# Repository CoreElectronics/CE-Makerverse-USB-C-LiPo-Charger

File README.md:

# Makerverse™ USB-C LiPo Charger

This is the repo for the Core Electronics [USB-C LiPo Charger](https://core-electronics.com.au/catalog/product/view/sku/ce08374).

The PCB layout project requires KiCAD 6.0 or newer to view. The schematic is provided in PDF format in the Documents folder.

## License
This project is open source - please review the LICENSE.md file for further licensing information.

If you have any technical questions, or concerns about licensing, please contact technical support on the [Core Electronics forums](https://forum.core-electronics.com.au/).

*\"PiicoDev\" and the PiicoDev logo are trademarks of Core Electronics Pty Ltd.*

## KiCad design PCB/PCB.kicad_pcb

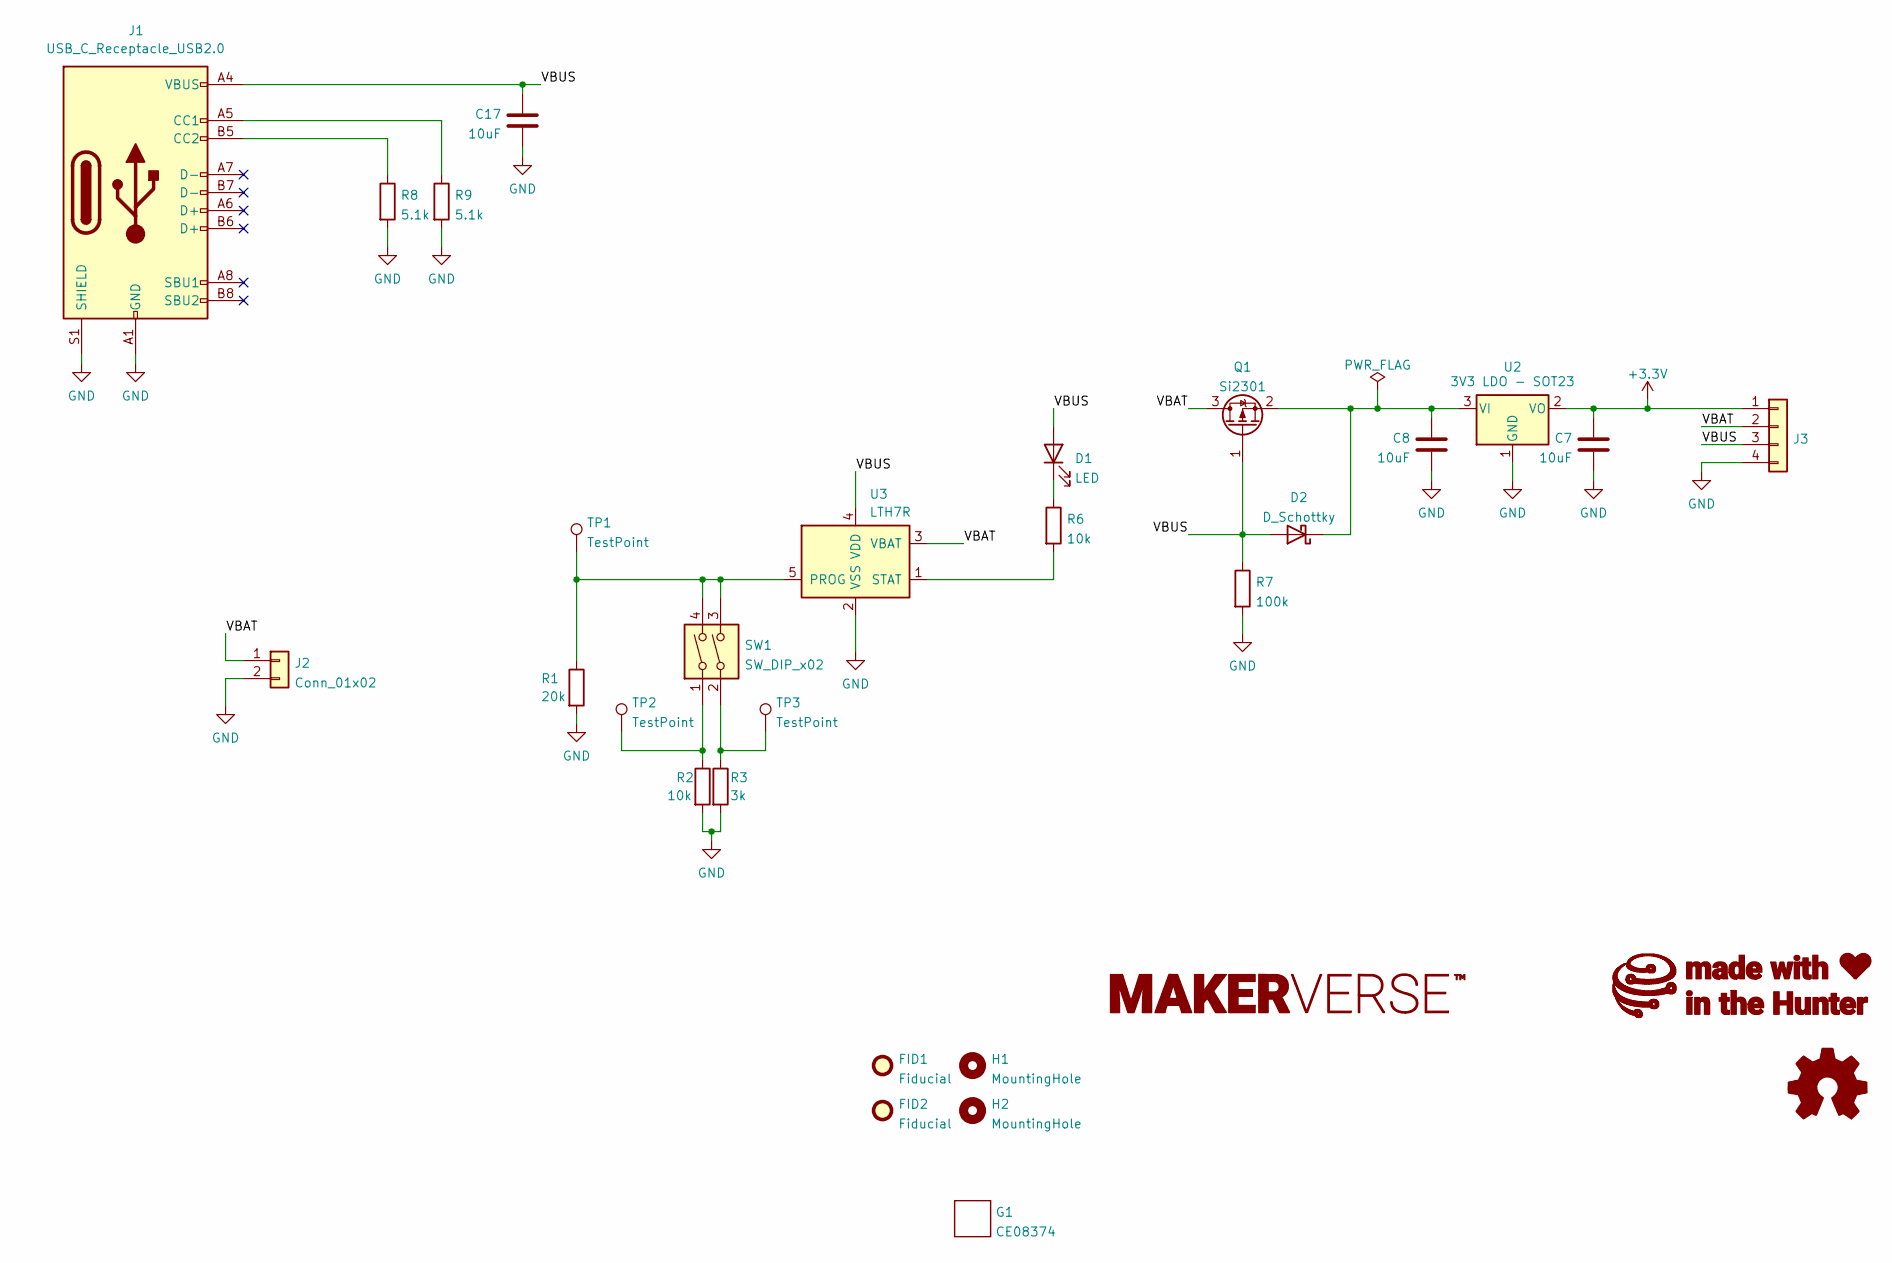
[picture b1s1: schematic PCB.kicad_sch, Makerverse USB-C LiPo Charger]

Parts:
C7, C8, C17: 10uF; C_0603_1608Metric
D1: LED; LED_0603_1608Metric
D2: D_Schottky; D_SMA
FID1, FID2: Fiducial; Fiducial_1mm_Mask2mm
G1: CE08374
G2: LOGO_Makerverse; makerverse_logo_short_14.0x2.4mm
H1, H2: MountingHole; MountingHole_3.2mm_M3
J1: USB_C_Receptacle_USB2.0; USB_C_Receptacle_HRO_TYPE-C-31-M-12
J2: Conn_01x02; JST_PH_S2B-PH-SM4-TB_1x02-1MP_P2.00mm_Horizontal
J3: Conn_01x04; PinHeader_1x04_P2.54mm_Vertical
LOGO1: Logo_Open_Hardware_Small; oshw_3.9x3.5mm
Q1: Si2301; SOT-23
R1: 20k; R_0402_1005Metric
R2, R6: 10k; R_0402_1005Metric
R3: 3k; R_0402_1005Metric
R7: 100k; R_0402_1005Metric
R8, R9: 5.1k; R_0402_1005Metric
SW1: SW_DIP_x02; SW_DIP_SPSTx02_Slide_Copal_CHS-02A_W5.08mm_P1.27mm_JPin
TP1, TP2, TP3: TestPoint; TestPoint_Pad_D1.5mm
U2: 3V3 LDO - SOT23; SOT-23
U3: LTH7R; SOT-23-5

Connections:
+3V3: C7.1, J3.1, U2.2 (VO)
/VBAT: J2.1, J3.2, Q1.3 (D), U3.3 (VBAT)
/VBUS: C17.1, D1.2 (A), D2.2 (A), J1.A4 (VBUS), J1.A9 (VBUS), J1.B4 (VBUS), J1.B9 (VBUS), J3.3, Q1.1 (G), R7.1, U3.4 (VDD)
GND: C7.2, C8.2, C17.2, J1.A1 (GND), J1.A12 (GND), J1.B1 (GND), J1.B12 (GND), J1.S1 (SHIELD), J2.2, J3.4, R1.2, R2.2, R3.2, R7.2, R8.2, R9.2, U2.1 (GND), U3.2 (VSS)
unnamed: C8.1, D2.1 (K), Q1.2 (S), U2.3 (VI)
unnamed: D1.1 (K), R6.1
unnamed: J1.A5 (CC1), R9.1
unnamed: J1.B5 (CC2), R8.1
unnamed: R1.1, SW1.3, SW1.4, TP1.1, U3.5 (PROG)
unnamed: R2.1, SW1.1, TP2.1
unnamed: R3.1, SW1.2, TP3.1
unnamed: R6.2, U3.1 (STAT)

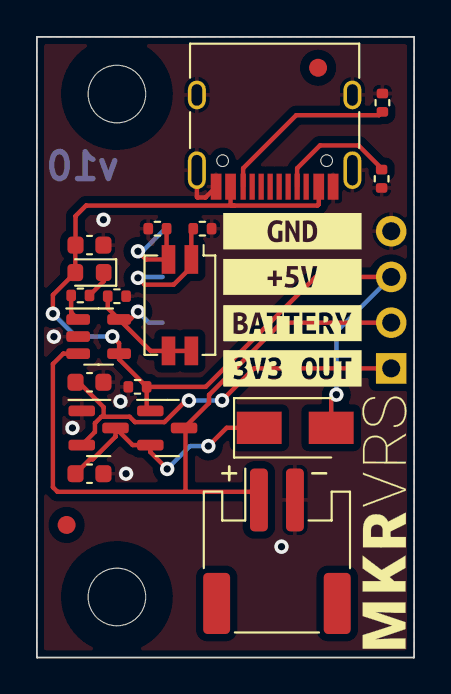
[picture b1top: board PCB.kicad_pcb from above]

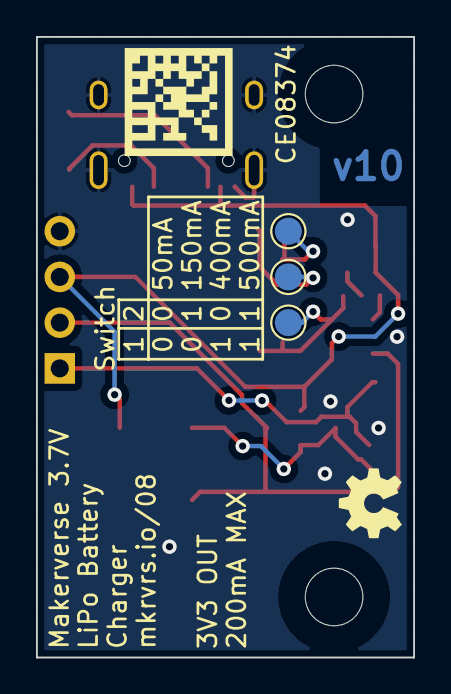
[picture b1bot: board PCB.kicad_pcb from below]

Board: 2 copper layers, 21.0 x 34.5 mm, 33 parts (5 on the bottom side), 12 nets.

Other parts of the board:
kibuzzard-6216C8F6: G***; kibuzzard-6216C8F6
kibuzzard-6216C913: G***; kibuzzard-6216C913
kibuzzard-6216CAF0: G***; kibuzzard-6216CAF0
kibuzzard-6216CB03: G***; kibuzzard-6216CB03

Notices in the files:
PCB/PCB.kicad_sch:
License: CCASAv4.0 https://creativecommons.org/licenses/by-sa/4.0
